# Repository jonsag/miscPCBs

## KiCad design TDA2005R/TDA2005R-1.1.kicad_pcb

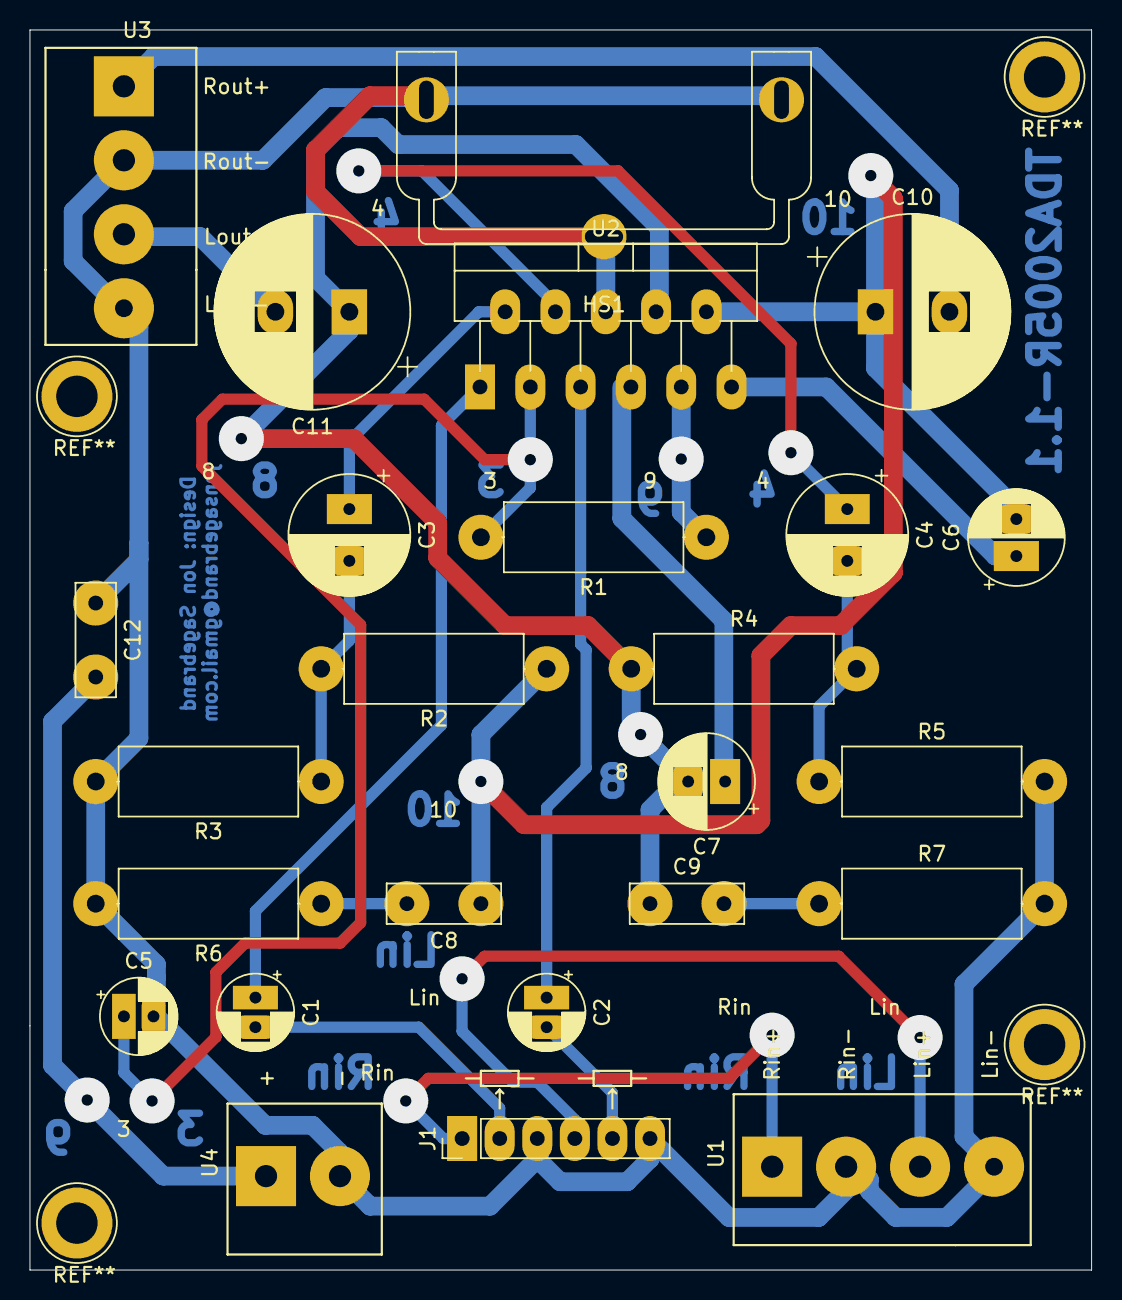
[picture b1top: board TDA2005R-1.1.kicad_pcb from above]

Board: 2 copper layers, 71.8 x 83.8 mm, 25 parts (0 on the bottom side), 21 nets.

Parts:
C1, C2: 2.2u; CP_Radial_D5.0mm_P2.00mm_larger
C3, C4: 220u; CP_Radial_D8.0mm_P3.50mm_large
C5: 10u; CP_Radial_D5.0mm_P2.00mm_larger
C6, C7: 100u; CP_Radial_D6.3mm_P2.50mm_large
C8, C9, C12: 0.1u; C_Disc_D7.5mm_W2.5mm_P5.00mm_larger
C10, C11: 2200u; CP_Radial_D13.0mm_P5.00mm_larger
HS1: Heatsink_Pad; EK-41002859
J1: 6-pole_dual_potentiometer_header; 6-pin_dual_potentiometer_header_large
R1: 120k; R_Axial_DIN0414_L11.9mm_D4.5mm_P15.24mm_Horizontal_larger
R2, R4: 1.2k; R_Axial_DIN0414_L11.9mm_D4.5mm_P15.24mm_Horizontal_larger
R3, R5: 33R; R_Axial_DIN0414_L11.9mm_D4.5mm_P15.24mm_Horizontal_larger
R6, R7: 1R; R_Axial_DIN0414_L11.9mm_D4.5mm_P15.24mm_Horizontal_larger
U1: 4-pole_RL-input_screw_terminal; 4-pole_screw_terminal_RL_input
U2: TDA2005; TO-220-11_P3.4x5.08mm_StaggerOdd_Lead4.85mm_Vertical_large
U3: 4-pole_RL-output_screw_terminal; 4-pole_screw_terminal_RL_output
U4: 2-pole_power_in_screw_terminal

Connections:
+15V: C12.2, R1.1, U2.9, U4.1
GND: C5.2, C12.1, HS1.1, J1.3, J1.6, R3.2, R5.2, R6.2, R7.2, U1.2, U1.4, U2.6, U3.2, U3.4, U4.2
Lin: J1.4, U1.3
Lout: C11.2, U3.3
unnamed: C1.1, U2.1
unnamed: C1.2, J1.2
unnamed: C2.1, U2.5
unnamed: C2.2, J1.5
unnamed: C3.1, U2.2
unnamed: C3.2, R2.2, R3.1
unnamed: C4.1, U2.4
unnamed: C4.2, R4.2, R5.1
unnamed: C5.1, R1.2, U2.3
unnamed: C6.1, U2.11
unnamed: C7.1, U2.7
unnamed: C8.2, R6.1
unnamed: C9.2, R7.1
unnamed: C6.2, C8.1, C10.1, R2.1, U2.10
unnamed: C7.2, C9.1, C11.1, R4.1, U2.8
Rin: J1.1, U1.1
Rout: C10.2, U3.1

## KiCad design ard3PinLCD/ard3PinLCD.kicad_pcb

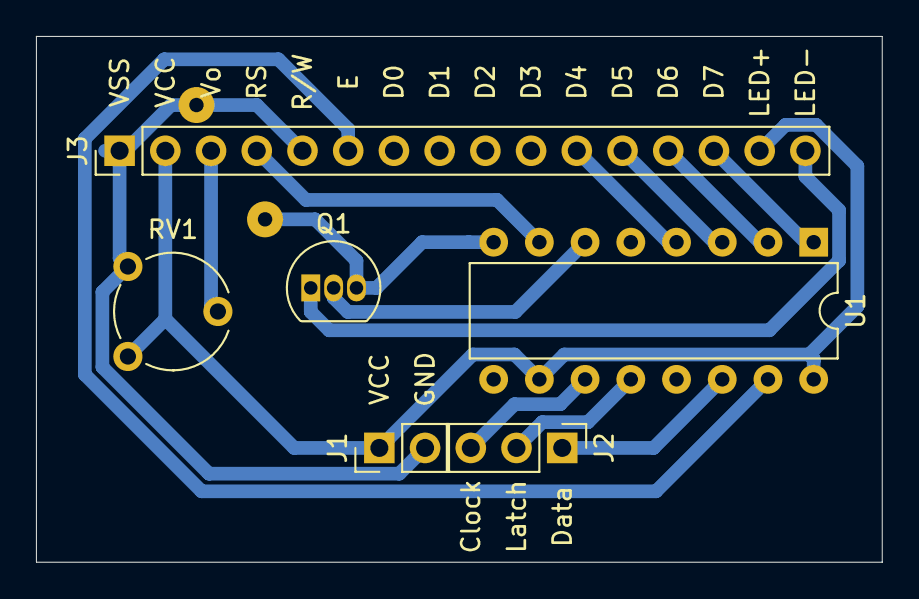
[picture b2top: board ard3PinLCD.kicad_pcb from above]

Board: 2 copper layers, 47.0 x 29.2 mm, 8 parts (0 on the bottom side), 14 nets.

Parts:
J1: 2-pin_power_input_header
J2: 3-pin_LCD_header
J3: 16-pin_LCD_header
J4, J5: Single_connector; Single_solder_pad
Q1: BC547; TO-92_Inline
RV1: LCD contrast; Potentiometer_Piher_PT-6-V_Vertical
U1: 74HC595; DIP-16_W7.62mm

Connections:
unnamed: J1.1, J3.2, J3.15, RV1.1, U1.10, U1.16
unnamed: J1.2, J3.1, J3.5, J4.1, J5.1, Q1.3, RV1.3, U1.8
unnamed: J2.1, U1.14
unnamed: J2.2, U1.12
unnamed: J2.3, U1.11
unnamed: J3.3, RV1.2
unnamed: J3.4, U1.7
unnamed: J3.6, U1.15
unnamed: J3.11, U1.4
unnamed: J3.12, U1.3
unnamed: J3.13, U1.2
unnamed: J3.14, U1.1
unnamed: J3.16, Q1.1
unnamed: Q1.2, U1.6

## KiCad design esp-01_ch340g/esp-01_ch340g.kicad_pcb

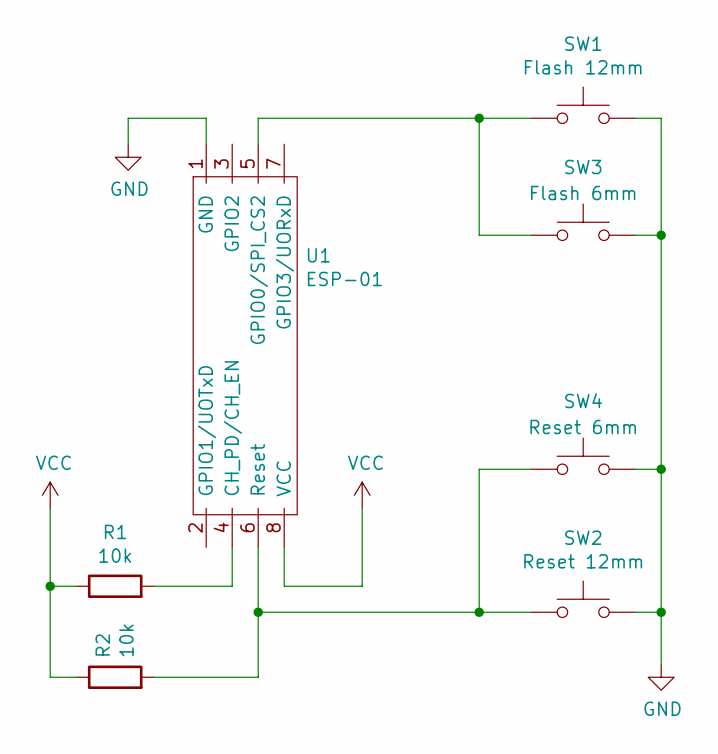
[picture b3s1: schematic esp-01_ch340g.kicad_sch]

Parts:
R1, R2: 10k; R_Axial_DIN0207_L6.3mm_D2.5mm_P10.16mm_Horizontal_larger_pa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
SW1: Flash 12mm; SW_PUSH-12mm_large
SW2: Reset 12mm; SW_PUSH-12mm_large
SW3: Flash 6mm; SW_PUSH_6mm_large
SW4: Reset 6mm; SW_PUSH_6mm_large
U1: ESP-01; ESP-01_w_pin_socket_large

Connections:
GND: SW1.2, SW2.2, SW3.2, SW4.2, U1.1 (GND)
unnamed: R1.2, U1.4 (CH_PD/CH_EN)
unnamed: R2.2, SW2.1, SW4.1, U1.6 (Reset)
unnamed: SW1.1, SW3.1, U1.5 (GPIO0/SPI_CS2)
VCC: R1.1, R2.1, U1.8 (VCC)

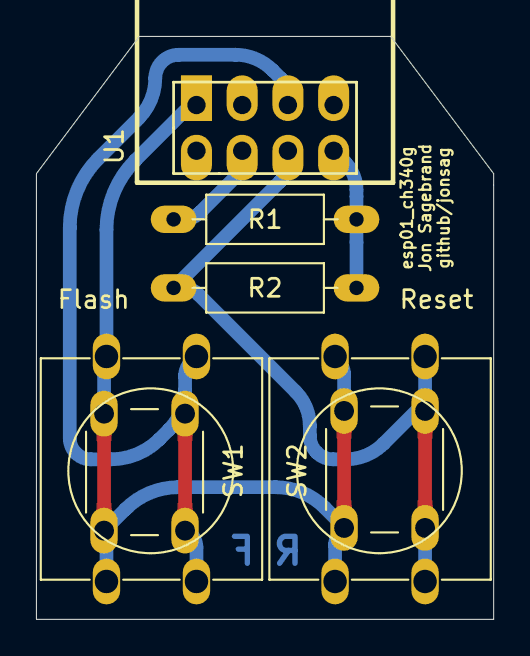
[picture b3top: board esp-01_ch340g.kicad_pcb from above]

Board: 2 copper layers, 25.4 x 32.4 mm, 7 parts (0 on the bottom side), 5 nets.
